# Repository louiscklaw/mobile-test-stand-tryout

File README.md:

### multiple mobile test stand
- #appium #testing #in-progress
-
- ### Fusion 360 path:
	- /home/projects/mobile-test-stand
	- https://a360.co/3NeUc2P
	-
-
- ### BOM/worksheet:
	- https://docs.google.com/spreadsheets/d/1pcP3x0ejMBr7scGuHOP2tLNko27h83g47JPfxIJjlhI
	-
- ### References:
	- https://www.printables.com/model/3407-articulating-raspberry-pi-camera-mount-for-prusa-m/files
-
- ### Repository
	- [https://github.com/louiscklaw/mobile-test-stand-tryout](https://github.com/louiscklaw/mobile-test-stand-tryout)
	- d:\\_workspace\mobile-test-stand-tryout
	-
- ### progress
	- 2022-10-28, design frozen, order 2020 profile @taobao
	-

### ref for stands

https://www.thingiverse.com/thing:1471349

https://www.thingiverse.com/thing:1478760

https://www.thingiverse.com/thing:706035

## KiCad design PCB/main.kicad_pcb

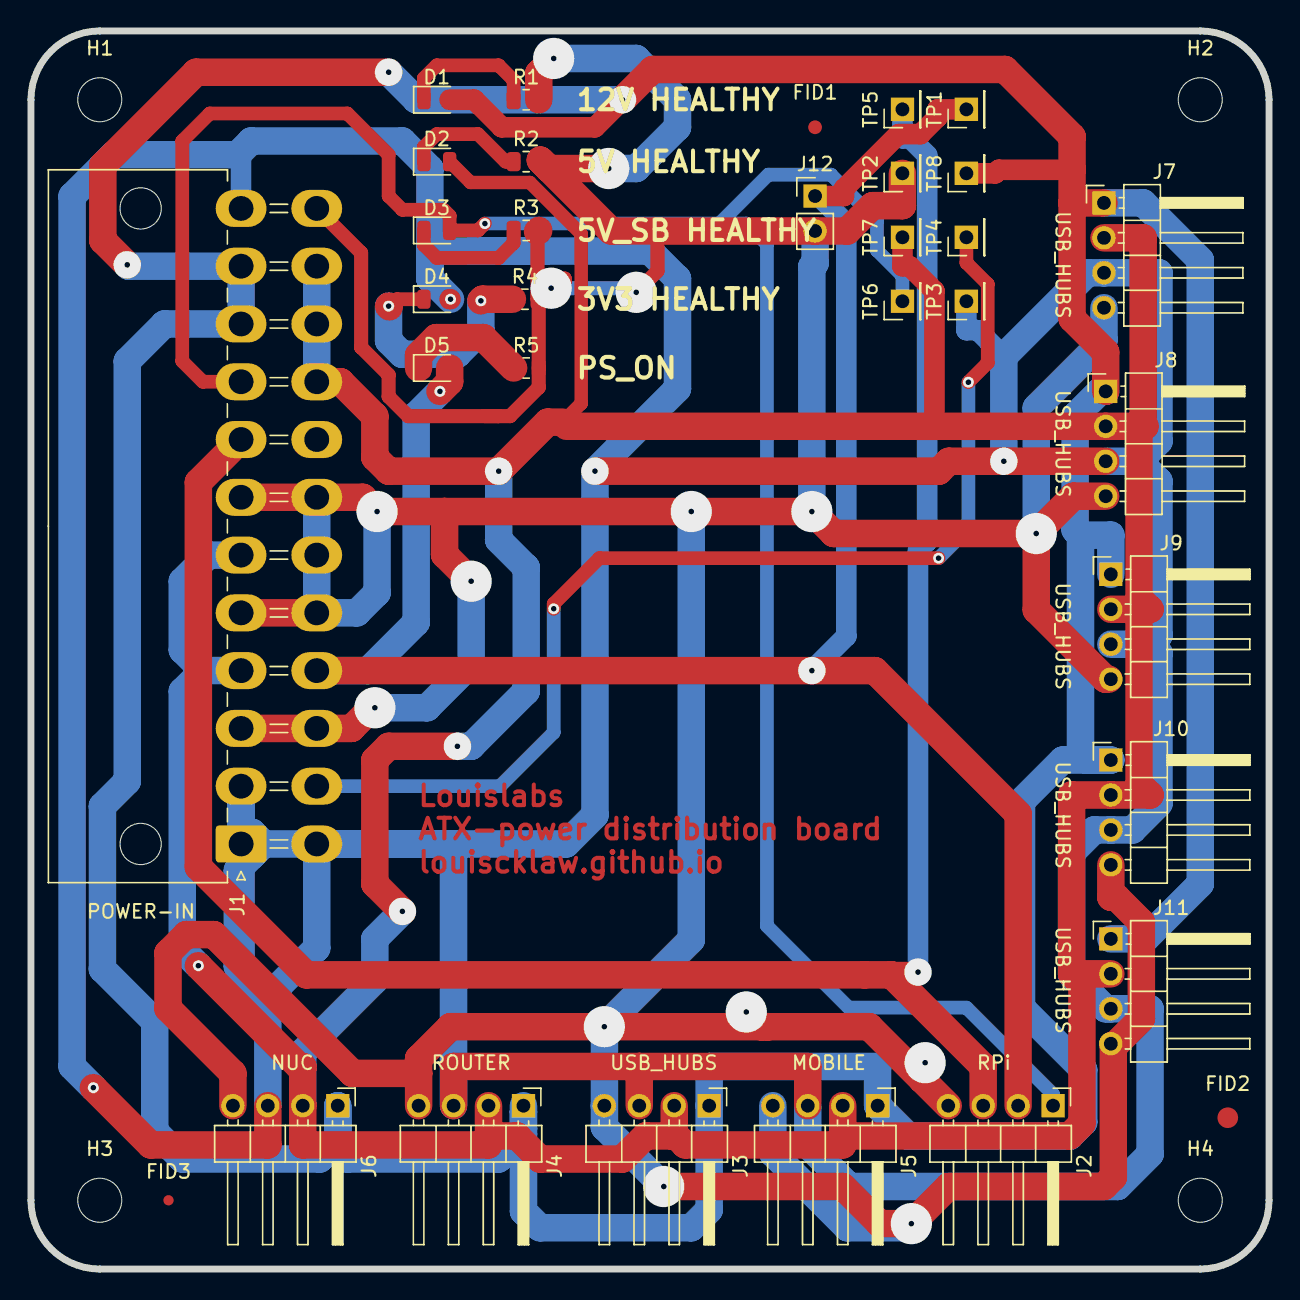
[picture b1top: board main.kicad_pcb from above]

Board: 2 copper layers, 90.0 x 90.0 mm, 37 parts (0 on the bottom side), 13 nets.

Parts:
D1, D2, D3, D4, D5: LED; D_0805_2012Metric
FID1: Fiducial; Fiducial_1mm_Mask3mm
FID2: Fiducial; Fiducial_1.5mm_Mask3mm
FID3: Fiducial; Fiducial_0.75mm_Mask2.25mm
H1, H2, H3, H4: MountingHole; MountingHole_3.2mm_M3_ISO14580
J1: ATX-24; Molex_Mini-Fit_Jr_5569-24A2_2x12_P4.20mm_Horizontal
J2: Conn_RPi; PinHeader_1x04_P2.54mm_Horizontal
J3, J7, J8, J9, J10, J11: Conn_USB_HUBS; PinHeader_1x04_P2.54mm_Horizontal
J4: Conn_Router; PinHeader_1x04_P2.54mm_Horizontal
J5: Conn_MOBILE; PinHeader_1x04_P2.54mm_Horizontal
J6: Conn_NUC; PinHeader_1x04_P2.54mm_Horizontal
J12: POWER_ON; PinHeader_1x02_P2.54mm_Vertical
R1: R331; R_0805_2012Metric
R2, R3: R221; R_0805_2012Metric
R4, R5: R102; R_0805_2012Metric
TP1, TP2, TP3, TP4, TP5, TP6, TP7, TP8: TestPoint; PinHeader_1x01_P2.54mm_Vertical

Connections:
/3V3: D4.2 (A), J1.1 (+3.3V), J1.2 (+3.3V), J1.12 (+3.3V), J1.13 (+3.3V), J3.3, J4.3, J5.3, J6.3, J7.3, J8.3, J9.3, J10.3, J11.3, TP3.1
/5V: D2.2 (A), J1.4 (+5V), J1.6 (+5V), J1.21 (+5V), J1.22 (+5V), J1.23 (+5V), J3.2, J4.2, J5.2, J6.2, J7.2, J8.2, J9.2, J10.2, J11.2, TP7.1
/5V_SB: D3.2 (A), J1.9 (+5VSB), J2.1, TP6.1
/12V: D1.2 (A), J1.10 (+12V), J1.11 (+12V), J3.1, J4.1, J5.1, J6.1, J7.1, J8.1, J9.1, J10.1, J11.1, TP8.1
/-12V: J1.14 (-12V), TP4.1
/PS_ON: D5.2 (A), J1.16 (PS_ON#), J2.2, J12.1, TP1.1
/PWR_OK: J1.8 (PWR_OK), J2.3, TP5.1
GND: J1.3 (GND), J1.5 (GND), J1.7 (GND), J1.15 (GND), J1.17 (GND), J1.18 (GND), J1.19 (GND), J1.24 (GND), J2.4, J3.4, J4.4, J5.4, J6.4, J7.4, J8.4, J9.4, J10.4, J11.4, J12.2, R1.2, R2.2, R3.2, R4.2, R5.2, TP2.1
unnamed: D1.1 (K), R1.1
unnamed: D2.1 (K), R2.1
unnamed: D3.1 (K), R3.1
unnamed: D4.1 (K), R4.1
unnamed: D5.1 (K), R5.1

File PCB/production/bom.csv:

Designator,Footprint,Quantity,Value,LCSC Part #,taobao link,
"D1, D2, D3, D4, D5",D_0805_2012Metric,5,LED,,N/A,
FID1,Fiducial_1mm_Mask3mm,1,Fiducial,,N/A,
FID2,Fiducial_1.5mm_Mask3mm,1,Fiducial,,N/A,
FID3,Fiducial_0.75mm_Mask2.25mm,1,Fiducial,,N/A,
"H1, H2, H3, H4",MountingHole_3.2mm_M3_ISO14580,4,MountingHole,,N/A,
J1,Molex_Mini-Fit_Jr_5569-24A2_2x12_P4.20mm_Horizontal,1,ATX-24,,https://item.taobao.com/item.htm?id=586680486947,?????5557/5569 4.2MM?????????????????
"J10, J11, J3, J7, J8, J9",PinHeader_1x04_P2.54mm_Horizontal,6,Conn_USB_HUBS,,https://item.taobao.com/item.htm?id=661768911099,KF2EDG-2.54mm
J12,PinHeader_1x02_P2.54mm_Vertical,1,POWER_ON,,https://item.taobao.com/item.htm?id=661768911099,KF2EDG-2.54mm
J2,PinHeader_1x04_P2.54mm_Horizontal,1,Conn_RPi,,https://item.taobao.com/item.htm?id=661768911099,KF2EDG-2.54mm
J4,PinHeader_1x04_P2.54mm_Horizontal,1,Conn_Router,,https://item.taobao.com/item.htm?id=661768911099,KF2EDG-2.54mm
J5,PinHeader_1x04_P2.54mm_Horizontal,1,Conn_MOBILE,,https://item.taobao.com/item.htm?id=661768911099,KF2EDG-2.54mm
J6,PinHeader_1x04_P2.54mm_Horizontal,1,Conn_NUC,,https://item.taobao.com/item.htm?id=661768911099,KF2EDG-2.54mm
R1,R_0805_2012Metric,1,R331,,,
"R2, R3",R_0805_2012Metric,2,R221,,,
"R4, R5",R_0805_2012Metric,2,R102,,,
"TP1, TP2, TP3, TP4, TP5, TP6, TP7, TP8",PinHeader_1x01_P2.54mm_Vertical,8,TestPoint,,N/A,

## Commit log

2019-12-05 init commit,
2020-05-06 ci: init travis build config,
2020-05-06 ci: init travis token,
2020-07-27 update,
2020-07-27 update readme,
2020-07-27 adding test-stand-with-camera,
2020-07-27 update multiple phone test stand,
2020-07-27 adding iphone models,
2020-07-27 adding phone models,
2020-07-27 ignore tee merge log,
2020-07-29 update draft design,
2022-11-07 update mobile-test-stand-tryout,
2022-11-14 update before fabrication,
